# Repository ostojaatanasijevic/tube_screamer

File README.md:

# TPI pedals - TBSCR

## Schematic

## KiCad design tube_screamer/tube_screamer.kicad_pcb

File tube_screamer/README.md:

# Tube screamer clone

## Schematic

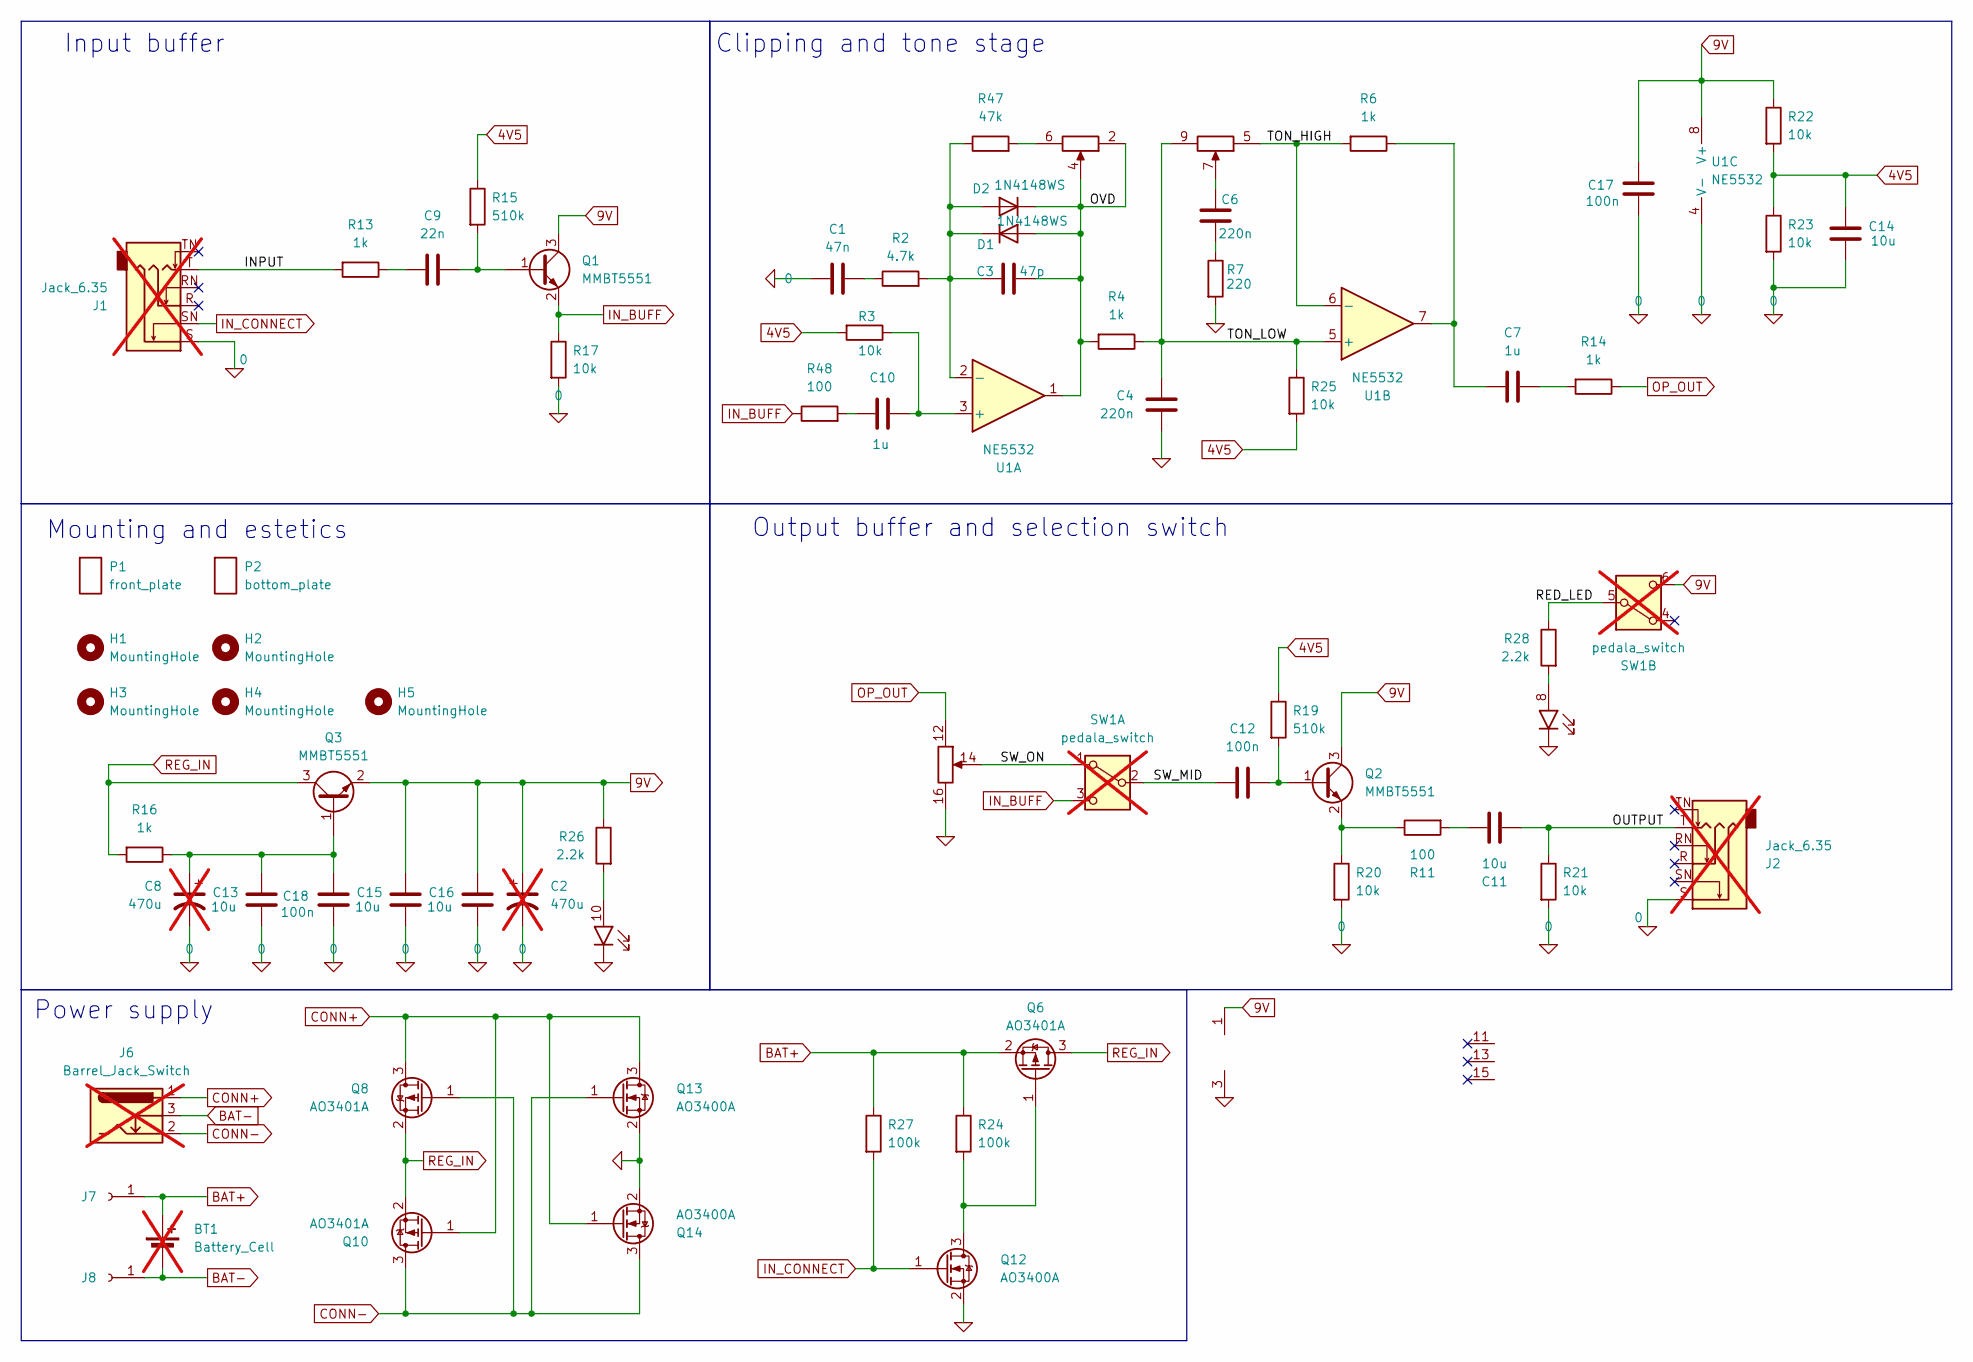
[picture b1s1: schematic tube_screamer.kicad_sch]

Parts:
BT1: Battery_Cell; BatteryHolder_Eagle_12BH611-GR; not fitted
C1: 47n; C_0603_1608Metric_Pad1.08x0.95mm_HandSolder; LCSC C1622
C2, C8: 470u; CP_Radial_D8.0mm_P3.50mm; not fitted
C3: 47p; C_0603_1608Metric_Pad1.08x0.95mm_HandSolder; LCSC C1671
C4, C6: 220n; C_0603_1608Metric_Pad1.08x0.95mm_HandSolder; LCSC C21120
C7, C10: 1u; C_0603_1608Metric_Pad1.08x0.95mm_HandSolder; LCSC C15849
C9: 22n; C_0603_1608Metric_Pad1.08x0.95mm_HandSolder; LCSC C21122
C11, C13, C14, C15, C16: 10u; C_0603_1608Metric_Pad1.08x0.95mm_HandSolder; LCSC C96446
C12, C17, C18: 100n; C_0603_1608Metric_Pad1.08x0.95mm_HandSolder; LCSC C14663
D1, D2: 1N4148WS; D_SOD-323; LCSC C2128
H1, H2, H3, H4, H5: MountingHole; M3_hole_with_spacer
J1, J2: Jack_6.35; Jack_6.35mm; not fitted
J6: Barrel_Jack_Switch; BarrelJack; not fitted
J7, J8: Conn_01x01_Socket; TestPoint_THTPad_D2.5mm_Drill1.2mm
J9: top_panel_connector; IDC-Header_2x08_P2.54mm_Vertical
P1: front_plate
P2: bottom_plate
Q1, Q2, Q3: MMBT5551; SOT-23; LCSC C2145
Q6, Q8, Q10: AO3401A; SOT-23; LCSC C15127
Q12, Q13, Q14: AO3400A; SOT-23; LCSC C20917
R2: 4.7k; R_0603_1608Metric_Pad0.98x0.95mm_HandSolder; LCSC C23162
R3, R17, R20, R21, R22, R23, R25: 10k; R_0603_1608Metric_Pad0.98x0.95mm_HandSolder; LCSC C25804
R4, R6, R13, R14, R16: 1k; R_0603_1608Metric_Pad0.98x0.95mm_HandSolder; LCSC C21190
R7: 220; R_0603_1608Metric_Pad0.98x0.95mm_HandSolder; LCSC C22962
R11, R48: 100; R_0603_1608Metric_Pad0.98x0.95mm_HandSolder; LCSC C22775
R15, R19: 510k; R_0603_1608Metric_Pad0.98x0.95mm_HandSolder; LCSC C23192
R24, R27: 100k; R_0603_1608Metric_Pad0.98x0.95mm_HandSolder; LCSC C25803
R26, R28: 2.2k; R_0603_1608Metric_Pad0.98x0.95mm_HandSolder; LCSC C4190
R47: 47k; R_0603_1608Metric_Pad0.98x0.95mm_HandSolder; LCSC C25819
SW1: pedala_switch; foot_switch_tht_no_pad; not fitted
U1: NE5532; SOIC-8_3.9x4.9mm_P1.27mm; LCSC C7426

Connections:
0: C1.1, C2.2, C4.1, C8.2, C13.2, C14.2, C15.2, C16.2, C17.1, C18.1, J1.S, J2.S, J9.3 (GND), J9.16, Q12.2 (S), Q13.2 (S), Q14.2 (S), R7.2, R17.2, R20.2, R21.2, R23.2, U1.4 (V-)
4V5: C14.1, R3.2, R15.1, R19.1, R22.2, R23.1, R25.2
9V: C2.1, C15.1, C16.1, C17.2, J9.1 (VCC), Q1.3 (C), Q2.3 (C), Q3.2 (E), R22.1, R26.1, SW1.6 (C), U1.8 (V+)
/INPUT: J1.T, R13.2
/OUTPUT: C11.2, J2.T, R21.1
/OVD: C3.2, D1.2 (A), D2.1 (K), J9.2, J9.4, R4.2, U1.1
/RED_LED: R28.1, SW1.5 (B)
/SW_MID: C12.1, SW1.2 (B)
/SW_ON: J9.14, SW1.1 (A)
/TON_HIGH: J9.5, R6.2, U1.6 (-)
/TON_LOW: C4.2, J9.9, R4.1, R25.1, U1.5 (+)
BAT+: BT1.1 (+), J7.1, Q6.2 (S), R24.1, R27.1
BAT-: BT1.2 (-), J6.3, J8.1
CONN+: J6.1, Q8.3 (D), Q10.1 (G), Q13.3 (D), Q14.1 (G)
CONN-: J6.2, Q8.1 (G), Q10.3 (D), Q13.1 (G), Q14.3 (D)
IN_BUFF: Q1.2 (E), R17.1, R48.1, SW1.3 (C)
IN_CONNECT: J1.SN, Q12.1 (G), R27.2
unnamed: C1.2, R2.1
unnamed: C6.2, R7.1
unnamed: C7.1, R6.1, U1.7
unnamed: C7.2, R14.2
unnamed: C9.1, R13.1
unnamed: C10.1, R48.2
unnamed: C11.1, R11.2
unnamed: C3.1, D1.1 (K), D2.2 (A), R2.2, R47.1, U1.2 (-)
unnamed: J9.6, R47.2
unnamed: C6.1, J9.7
unnamed: J9.8, R28.2
unnamed: J9.10, R26.2
unnamed: C9.2, Q1.1 (B), R15.2
unnamed: C12.2, Q2.1 (B), R19.2
unnamed: Q2.2 (E), R11.1, R20.1
unnamed: C8.1, C13.1, C18.2, Q3.1 (B), R16.1
unnamed: Q6.1 (G), Q12.3 (D), R24.2
unnamed: C10.2, R3.1, U1.3 (+)
OP_OUT: J9.12, R14.1
REG_IN: Q3.3 (C), Q6.3 (D), Q8.2 (S), Q10.2 (S), R16.2

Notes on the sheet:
Input buffer
Mounting and estetics
Clipping and tone stage
Output buffer and selection switch
Power supply

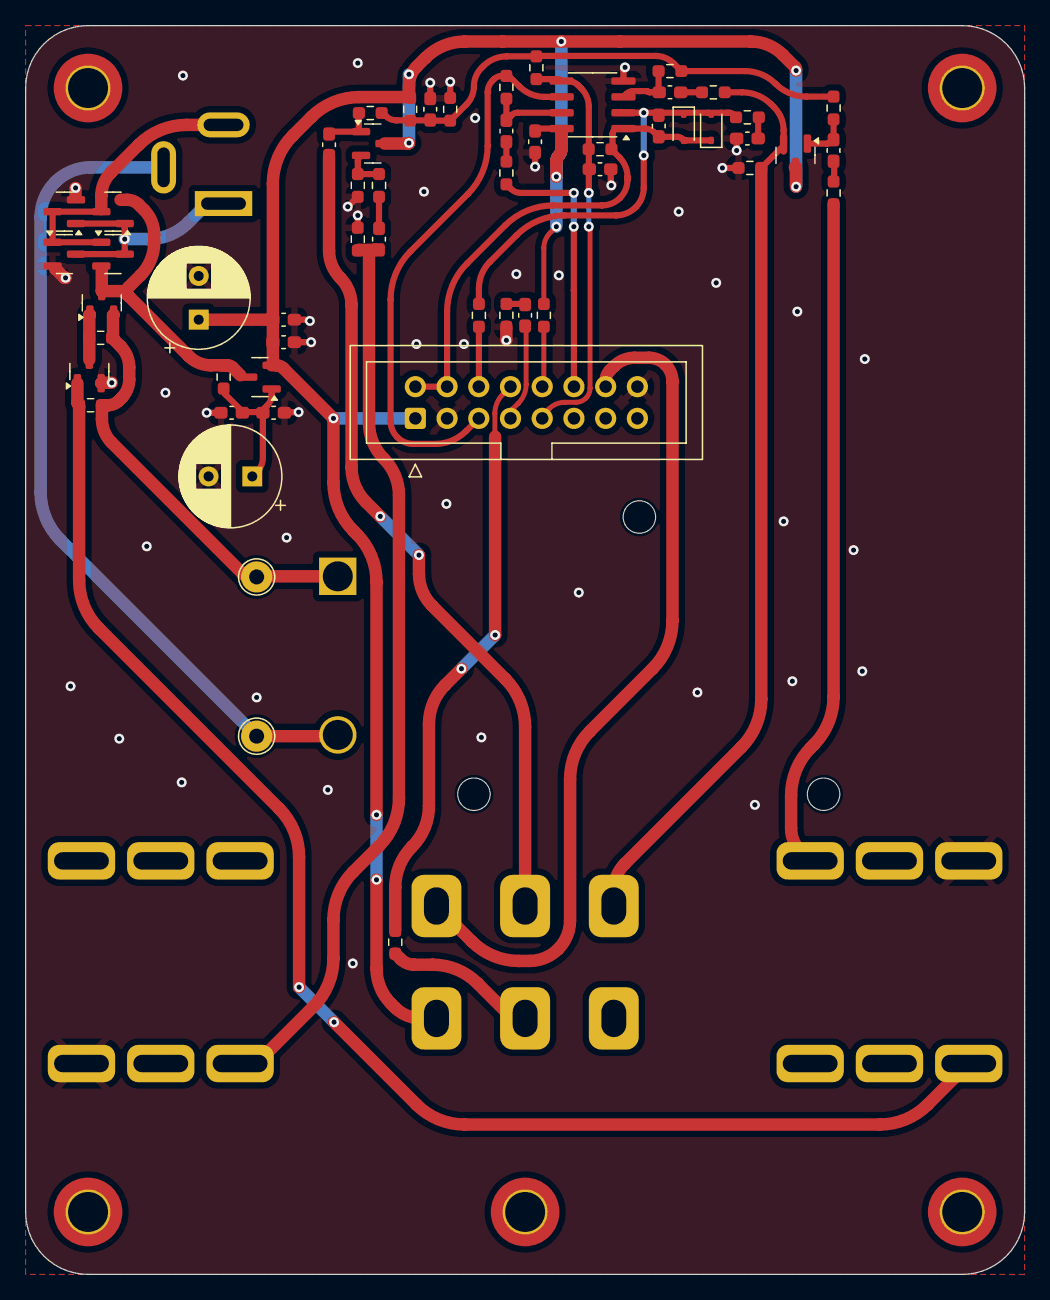
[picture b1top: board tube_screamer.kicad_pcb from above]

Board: 2 copper layers, 80.0 x 100.0 mm, 67 parts (0 on the bottom side), 37 nets.

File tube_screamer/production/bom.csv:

Designator,Footprint,Quantity,Value,LCSC Part #
C1,0603,1,47n,C1622
"C10, C7",0603,2,1u,C15849
"C11, C13, C14, C15, C16",0603,5,10u,C96446
"C12, C17, C18",0603,3,100n,C14663
C3,0603,1,47p,C1671
"C4, C6",0603,2,220n,C21120
C9,0603,1,22n,C21122
"D1, D2",D_SOD-323,2,1N4148WS,C2128
"Q1, Q2, Q3",SOT-23,3,MMBT5551,C2145
"Q10, Q6, Q8",SOT-23,3,AO3401A,C15127
"Q12, Q13, Q14",SOT-23,3,AO3400A,C20917
"R11, R48",0603,2,100,C22775
"R13, R14, R16, R4, R6",0603,5,1k,C21190
"R15, R19",0603,2,510k,C23192
"R17, R20, R21, R22, R23, R25, R3",0603,7,10k,C25804
R2,0603,1,4.7k,C23162
"R24, R27",0603,2,100k,C25803
"R26, R28",0603,2,2.2k,C4190
R47,0603,1,47k,C25819
R7,0603,1,220,C25804
U1,SOIC-8_3.9x4.9mm_P1.27mm,1,NE5532,C7426

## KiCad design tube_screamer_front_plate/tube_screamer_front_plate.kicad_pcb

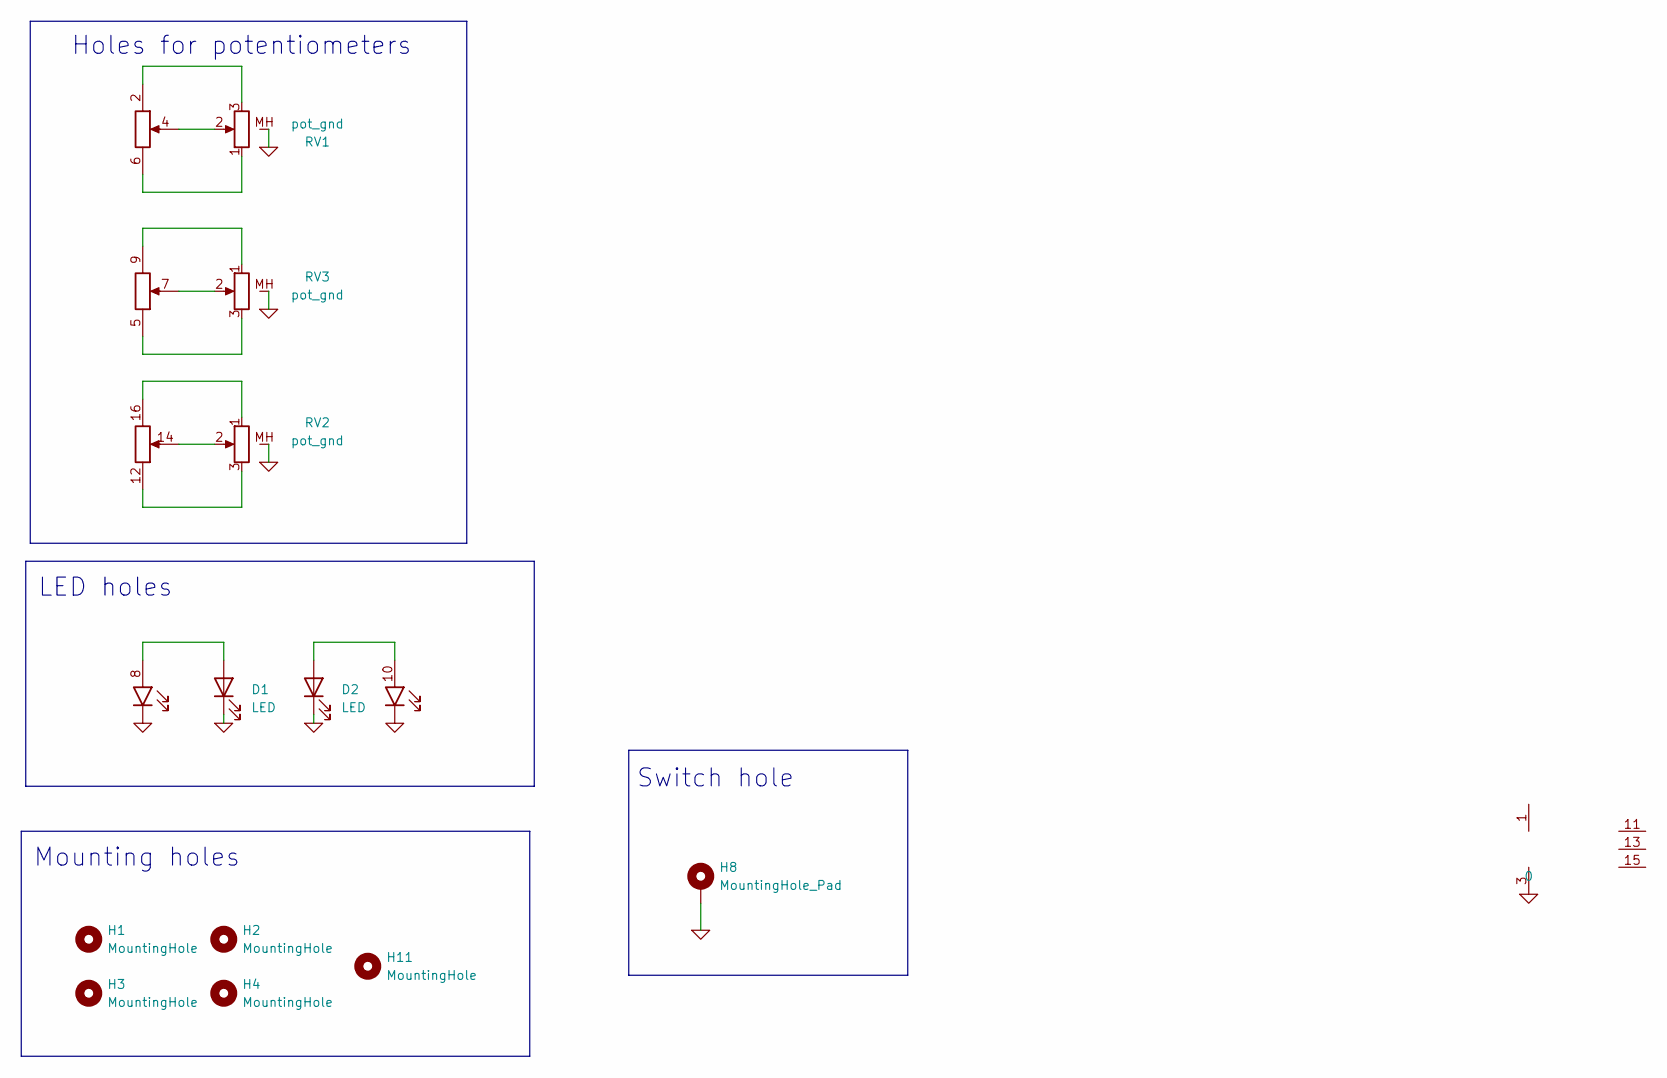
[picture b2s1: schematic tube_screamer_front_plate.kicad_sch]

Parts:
D1: LED; red_led
D2: LED; green_led
H1, H2, H3, H4, H11: MountingHole; MountingHole_3.2mm_M3_DIN965_Pad_TopBottom
H8: MountingHole_Pad; plated_switch_hole
J1: top_panel_connector; IDC-Header_2x08_faux_SMD
RV1, RV2, RV3: pot_gnd; top_plate_pot

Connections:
0: D1.1 (K), D2.1 (K), H8.1, J1.3 (GND), RV1.MH (2), RV2.MH (2), RV3.MH (2)
unnamed: D1.2 (A), J1.8
unnamed: D2.2 (A), J1.10 (1)
unnamed: J1.2, RV1.3
unnamed: J1.4, RV1.2
unnamed: J1.6, RV1.1
unnamed: J1.5, RV3.3
unnamed: J1.7, RV3.2
unnamed: J1.9, RV3.1
unnamed: J1.12, RV2.3
unnamed: J1.14, RV2.2
unnamed: J1.16, RV2.1

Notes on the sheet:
Holes for potentiometers
LED holes
Mounting holes
Switch hole

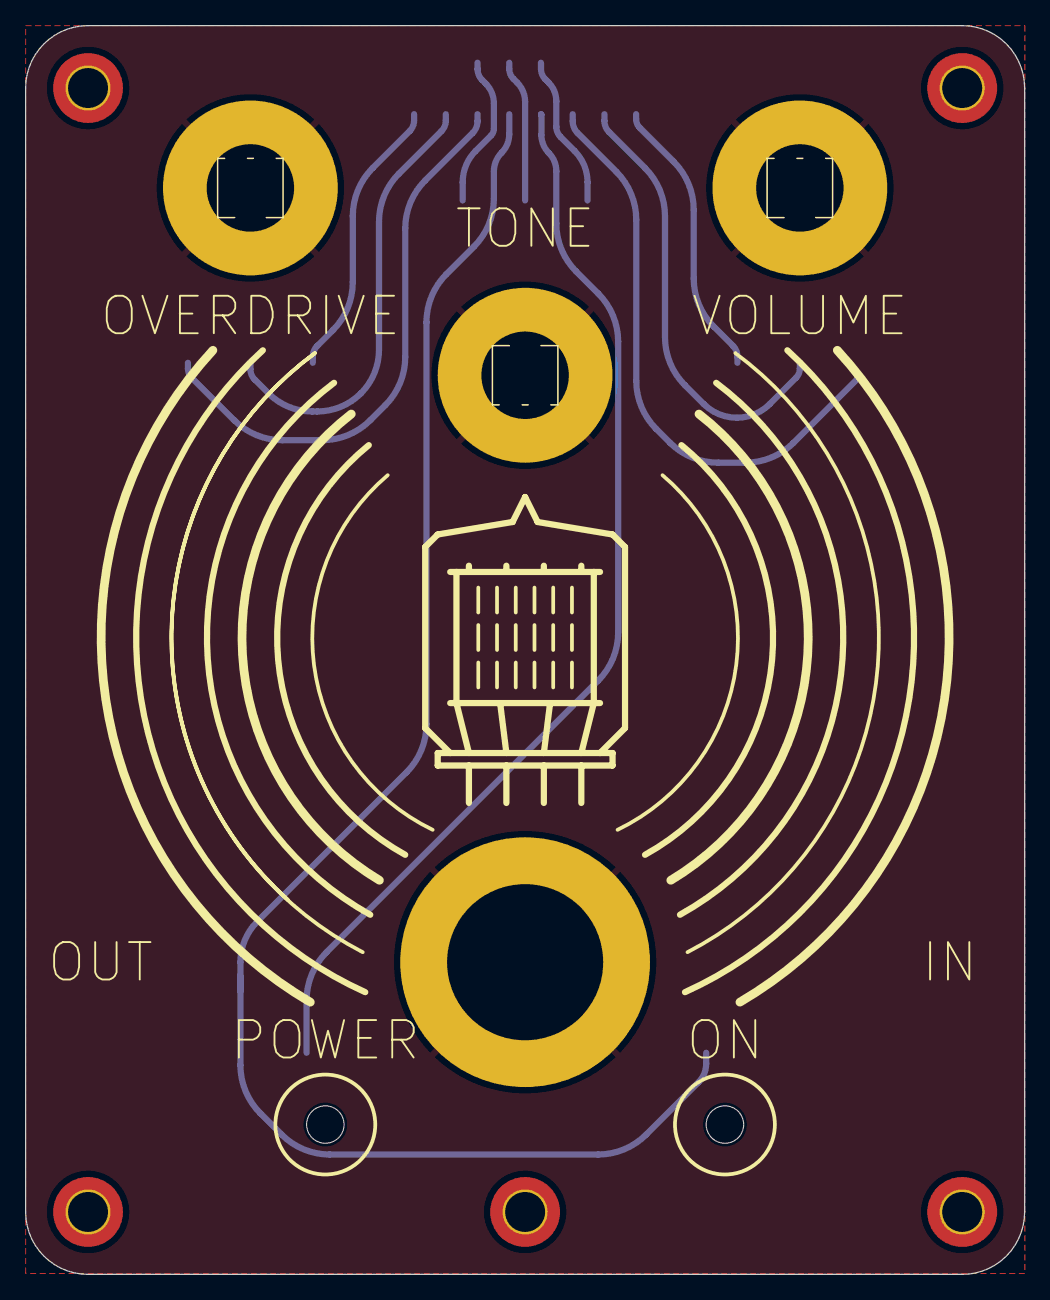
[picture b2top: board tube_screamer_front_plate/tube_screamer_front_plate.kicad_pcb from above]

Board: 2 copper layers, 80.0 x 100.0 mm, 12 parts (1 on the bottom side), 12 nets.

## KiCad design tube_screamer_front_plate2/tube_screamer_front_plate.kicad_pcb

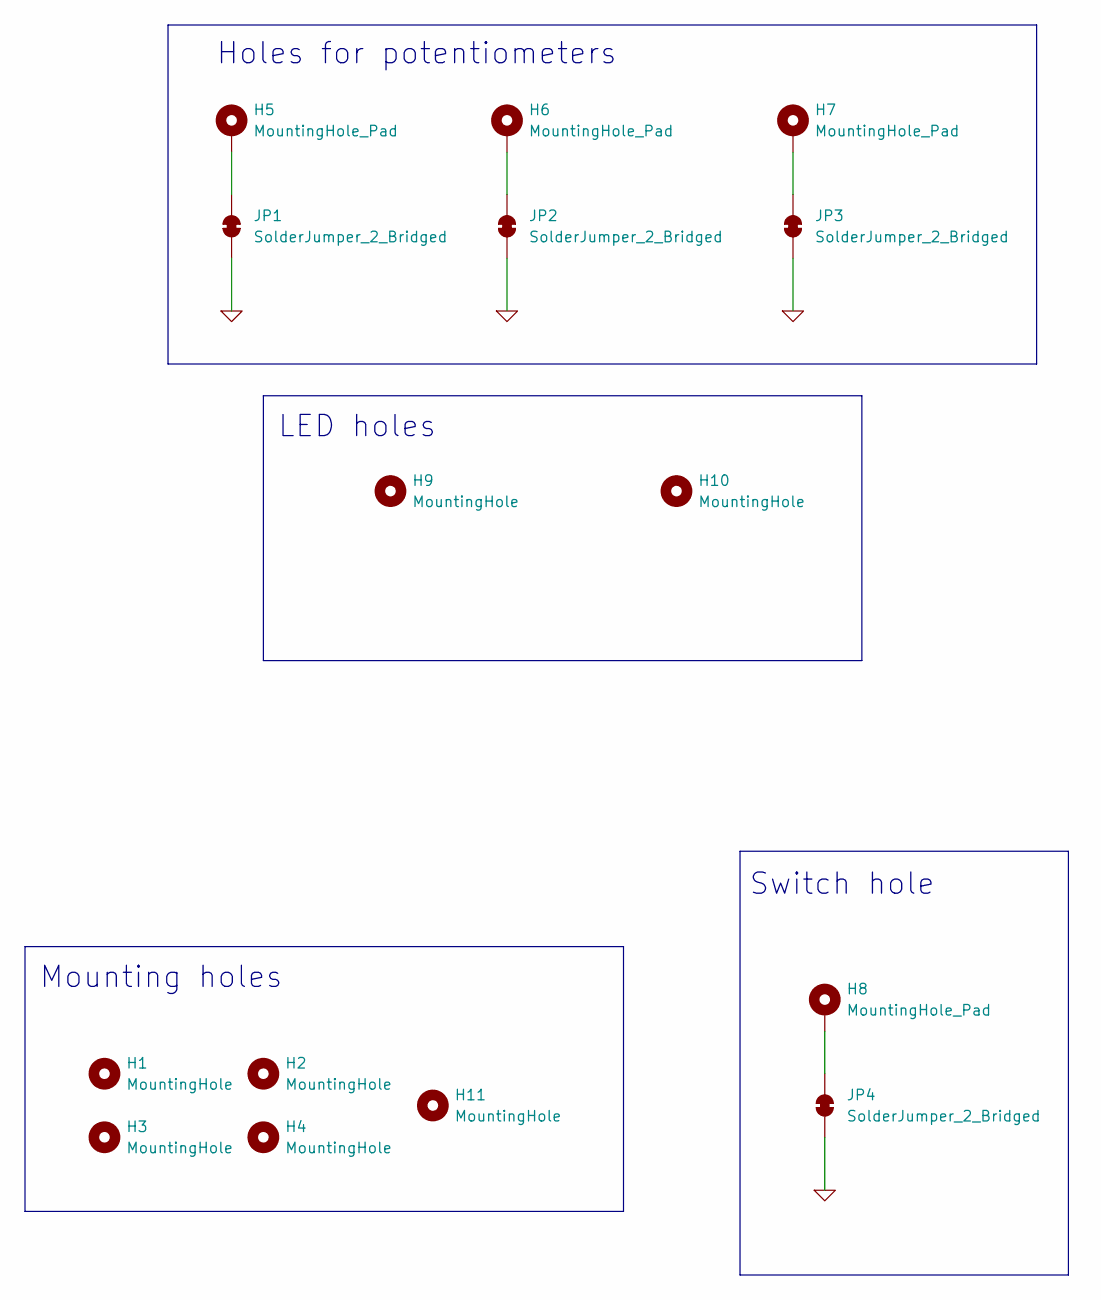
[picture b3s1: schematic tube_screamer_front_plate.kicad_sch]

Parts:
H1, H2, H3, H4, H11: MountingHole; MountingHole_3.2mm_M3_DIN965_Pad_TopBottom
H5, H6, H7: MountingHole_Pad; plated_pot_hole
H8: MountingHole_Pad; plated_switch_hole
H9, H10: MountingHole; MountingHole_3mm
JP1, JP2, JP3, JP4: SolderJumper_2_Bridged; SolderJumper-2_P1.3mm_Bridged_RoundedPad1.0x1.5mm

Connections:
0: JP1.1 (A), JP2.1 (A), JP3.1 (A), JP4.1 (A)
unnamed: H5.1, JP1.2 (B)
unnamed: H6.1, JP2.2 (B)
unnamed: H7.1, JP3.2 (B)
unnamed: H8.1, JP4.2 (B)

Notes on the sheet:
Mounting holes
Switch hole
LED holes
Holes for potentiometers

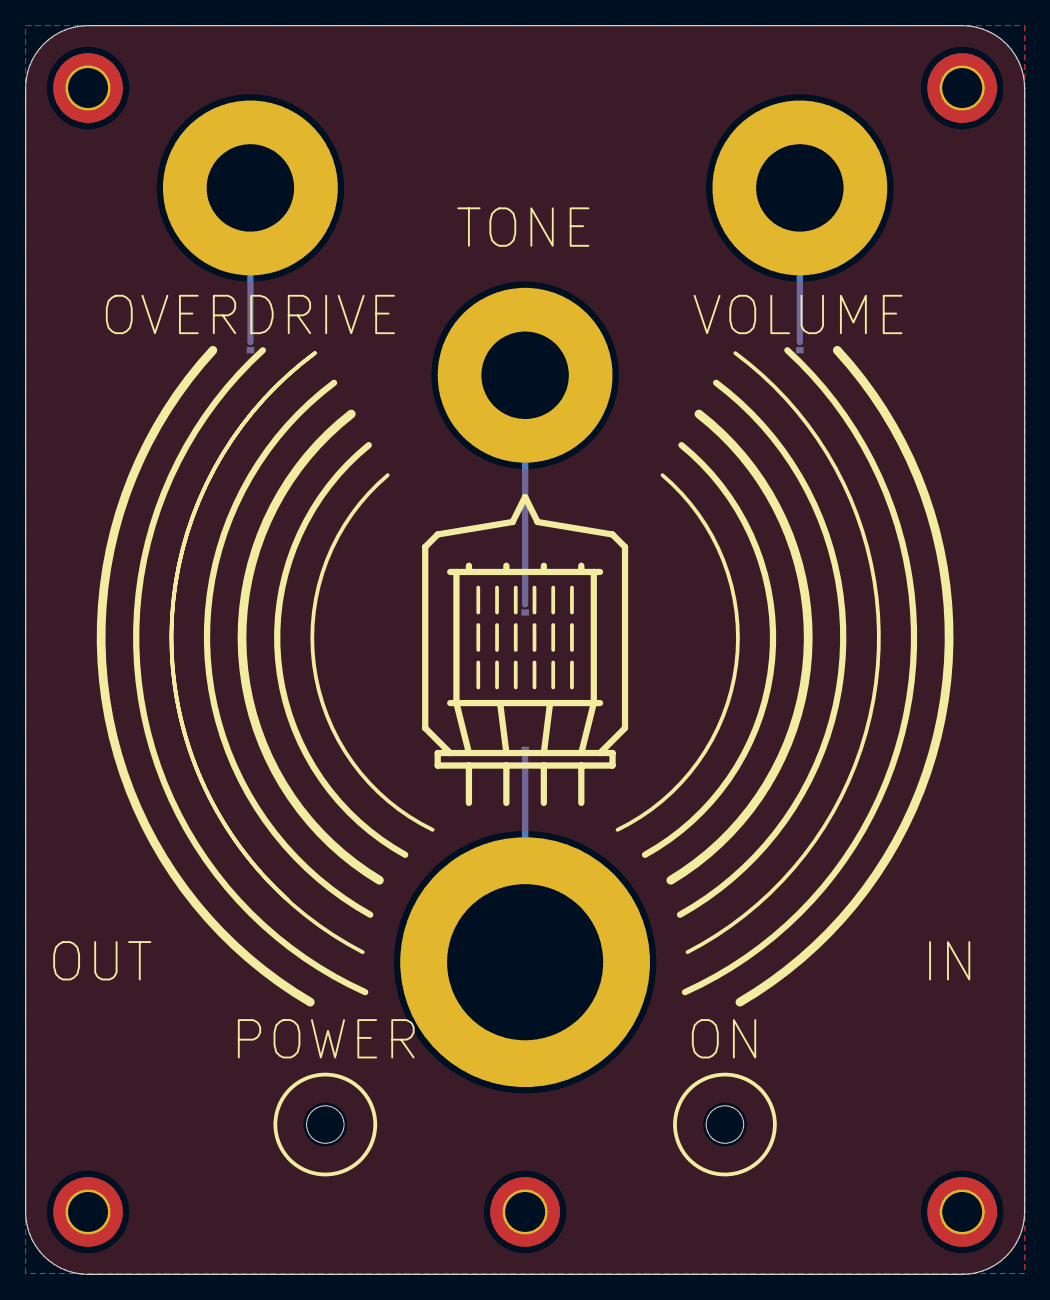
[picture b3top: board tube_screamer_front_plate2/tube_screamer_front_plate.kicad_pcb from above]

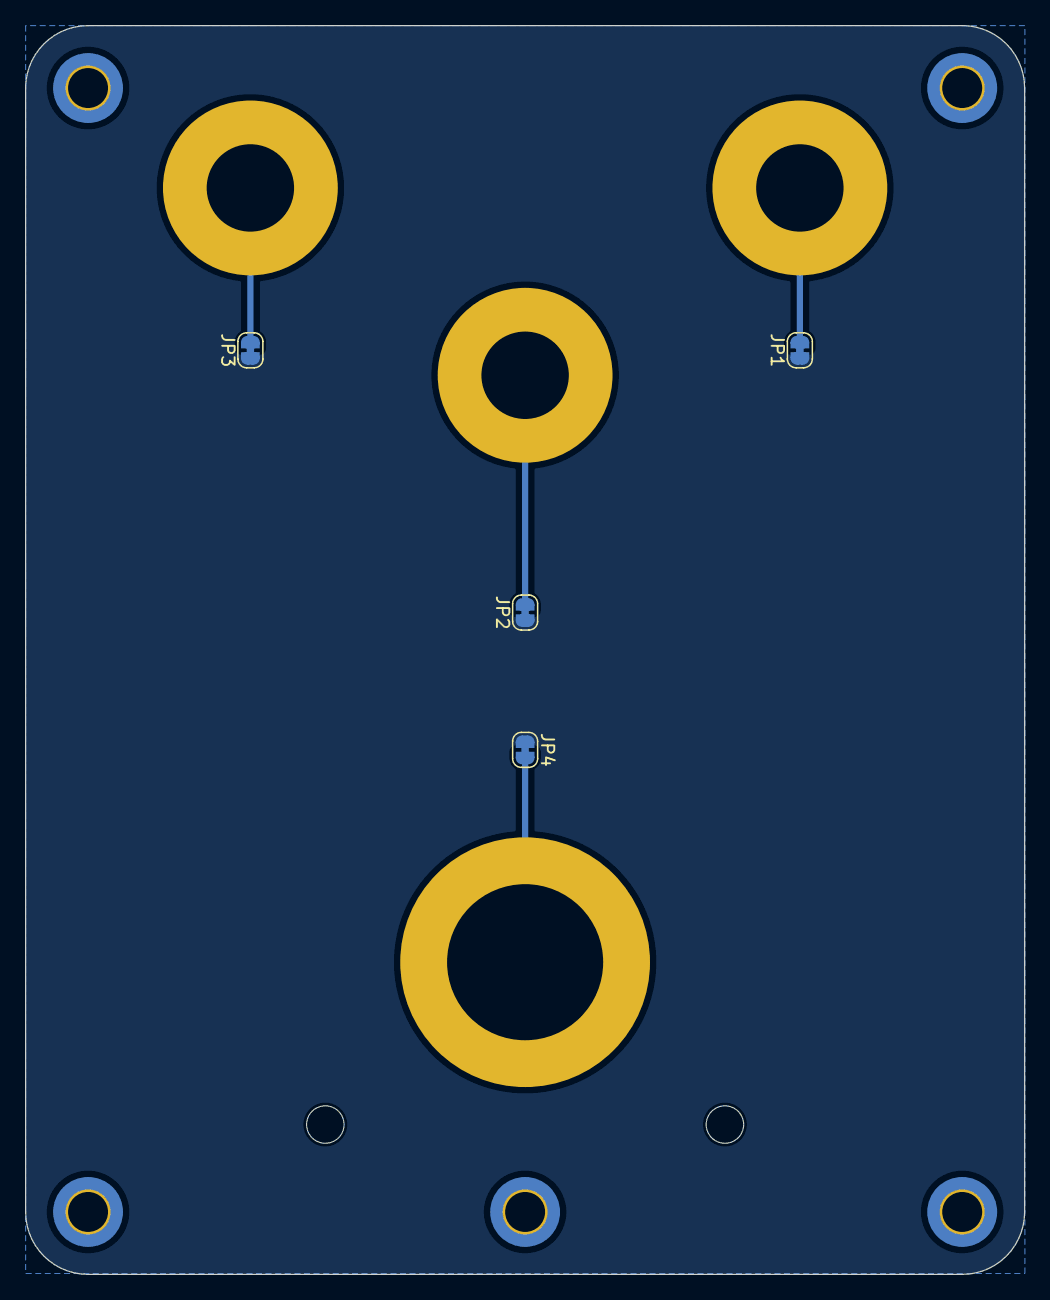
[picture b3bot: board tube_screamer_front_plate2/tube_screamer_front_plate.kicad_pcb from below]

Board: 2 copper layers, 80.0 x 100.0 mm, 15 parts (4 on the bottom side), 5 nets.

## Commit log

2025-03-29 Init.
2025-03-29 PCB layout.
2025-03-29 PCB update.
2025-03-30 Updated schematic
2025-03-30 Updated schematic and layout.
2025-03-30 poredjani potenciometri, layout na pola puta
2025-03-30 Changed opamp to NE5532, basic LCSC part.
2025-03-31 Added switch connectors.
2025-03-31 Updated switch, added diode.
2025-04-01 Added connectors and switch.
2025-04-01 Polacko
2025-04-01 new lib
2025-04-02 Goin well.
2025-04-02 3D bodies
2025-04-02 Schematic cleaned.
2025-04-02 Schem fix
2025-04-02 Fixx.
2025-04-02 povezano
2025-04-03 Schematic fix, PCB final
2025-04-05 All errors removed
2025-04-06 Production files v1.
2025-04-20 Rotirani pinovi audio konektora, rotirani LED prekidač pinovi.
2025-05-06 New management.
2025-05-06 Renamve
2025-05-06 new mna
2025-05-09 Top plate update.
2025-05-09 Pots fit, battery holder has to be moved.
2025-05-09 Update library.
2025-05-13 Added bottom plate.
2025-05-13 added script.
2025-05-13 Generated models.
2025-05-13 Updated, added 3d bodies.
2025-05-13 Update schematic.
2025-05-14 1 Red, 3 green connector.
2025-05-14 Pots checked, all good.
2025-05-19 Fixed diodes on front plate, fixed power schem.
2025-05-21 Updated libraries.
2025-05-21 IDC connector moved.
2025-05-21 Tube screamer front plate done, library updated.
2025-05-21 GND to top.
2025-05-22 Checklist done, only layout left.
2025-05-22 Added label to front plate botom.
2025-05-22 2.2 kOhm LED resistance.
2025-05-22 Top plate rounded.
2025-05-22 dafsd
2025-05-22 Updated 3D bodies.
2025-05-24 Layout done.
2025-05-24 kjflsad.
2025-05-24 Done.
2025-05-24 Ready for production.
2025-05-24 Readme update.
2025-05-24 readme
